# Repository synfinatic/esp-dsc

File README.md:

# ESP-DSC: Digital Setting Circles for ESP-12E/F

## About

Low cost alternative to my original Digital Setting Circles project the
[Teensy-DSC](https://github.com/synfinatic/teensy-dsc/).  This new design
uses the cheap ESP-12E/F WiFi enabled microcontroller which saves about 60% 
of the original price (~$40 vs ~$100).

I'm also planing to include the necessary .STL files so you can 3D print
the appropriate enclosure for the board.

More information about this project is available [on my website](https://synfin.net/sock_stream/tag/esp-dsc).

## v1.2 Status

 * Design PCB (complete!)
 * Port over the TeensyDSC code to the ESP-12 (complete!)
 * Verify that the ESP-12E is capable of handeling 2.5K PPR/10K count encoders (complete!)
 * Verify that the ESP-12E is capable of handeling 10K PPR/40K count encoders (failed!)
 * Create the necessary STL files to 3D print an enclosure for the board (complete!)
 * Major board change between v1.0 and v1.1- different pins used!

## v2.0 Status 
 * Redesign PCB for better performance  (TBD)
 * Update code based on new design (TBD)
 * Verify that the ESP-12E is capable of handeling 10k encoders (TBD)

## Performance

So a quick word about performance.  There are a number of people who claim that 
the ESP-12E has enough horsepower for two 2500PPR (10K after quadurature decoding) 
encoders.  One person told me they saw some errors, but they were small and 
likely caused by their mount.  This didn't seem very scientific to me, so I ran 
some tests.

My methodolgy is pretty simple.  I connected two ESP12E's to the same set of 
encoders.  Both ESP12E's used the same code and a custom modified version of 
[Paul Stoffgren's Encoder library](https://github.com/PaulStoffregen/Encoder) 
which has support for the ESP8266.  I also glued a toothpick to each encoder 
shaft to make it easier to rotate with my finger.  The test would be simple: If
both ESP12E's reported the same values, then I would say it was accurate.  But 
if the results were different, then it wasn't accurate.

I found that I could rotate a single 2,500PPR as fast as I possibly could 
without any error.  I could rotate a single 10,000PPR (40K after quadurature 
decoding) almost as fast without causing any error.

However, once I introduced a second encoder, I started seeing errors.  At about 
1 rotation/second, the 2500PPR encoders started to show some errors.  Two 
10,000PPR encoders had significant errors.  I also noticed that "flicking" the 
encoder causing it to quickly accellerate for a short duration (approx 1/4 
to 1/2 rotation) would cause significant errors even with the 2500PPR encoders.

This indicates that a person who does not very quickly move their scope 
should be able to use two 2500PPR encoders without introducing any 
errors.  If you're using a GoTo mount or a large scope you should be very 
safe.

I've done some testing on my AD12 (12" dobsonian) and 2500PPR/10,000 "count" 
encoders and found accuracy wasn't a problem at all.  The amount of error I saw
was approximagely +/-0.25deg meaning that if you have an EP with a 0.60deg 
effective FOV or more you should be able to use the ESP-DSC to point at an 
object and have it located inside your view through the scope.  Considering 
this is a mass produced dobsonian with a particile board mount, I consider 
this effectively within the error of the mount itself.

For comparison, my 30deg/82FOV Explore Scientific EP has an effective FOV of 
1.62deg in my scope which is more then twice the minimum.  

However I don't feel that it would be reliably accurate using 10,000PPR 
(40K count) encoders.  The result is I don't feel my initial PCB design is 
good enough with a single ESP12E.  I'm currently researching other solutions 
which could be implemented as cheaply and reliably as possible.

## Basic Features
I wanted to do my own digital setting circles (DSC) for my Apertura AD12.
The main goals were:

 * Support for at least 40K resolution via quadurature decoding (10k encoders)
 * Built in WiFi access point to allow wirelessly interfacing to an Apple iPad or Android tablet
 * Supporting at least [SkySafari Plus/Pro](http://www.skysafariastronomy.com/)
 * Powered via USB connection
 * Using industry standard RJ45 connection to encoders
 * Open source software & PCB design (GPLv3)
    * PCB Design done in [KiCad](http://www.kicad.org)
    * PCB's available from [OshPark](http://www.oshpark.com)
 * Inexpensive!  All the components should be available for < $40.

## Programming
You will need the Arduino 1.8.1+ IDE.   You will need to add support for the 
ESP8266 by [following the directions here](https://github.com/esp8266/Arduino).

Before you program your ESP-DSC you will need to:
 * Copy src/esp_dsc/config.h.sample to src/esp_dsc/config.h 
 * edit src/esp_dsc/config.h 

Under the tools menu, configure your board as follows:
 * Board: NodeMCU 1.0 (ESP-12E Module)
 * Flash Size: 4M (3M SPIFFS)
 * CPU Frequency: 80Mhz
 * Upload Speed: 115200 Baud

Do the following *exactly*:

 1. Disconnect the ESP-DSC from the encoders
 1. Connect a FTDI board to the FTDI header on the ESP-DSC and plug that into your computer
 1. Select the FTDI as your serial port in the Arduino IDE Tools menu
 1. Press and hold the Reset button
 1. Press and hold the Program button
 1. Release Reset button
 1. Release Program button
 1. Press the Upload button in the Arduino IDE Tools menu

## Supported Software

 * SkySafari Plus/Pro 
    - Select "Basic Encoder System"
    - Encoder Steps: Get Automatically
    - TCP Port 4030

## Similar Projects
There are a bunch of similar projects to ESP-DSC which you should be aware of:
 * [TeensyDSC](https://github.com/synfinatic/teensy-dsc/)
 * [Dave Ek's Setting Circles](http://eksfiles.net/digital-setting-circles/)
 * [mrosseel/arduino-dsc](https://github.com/mrosseel/arduino-dsc)
 * [mdw123/arduino-dsc](https://github.com/mdw123/arduino-dsc)
 * [Arduino Bluetooth DSC](http://orlygoingthirty.blogspot.com/2012/01/arduino-bluetooth-digital-setting.html)
 * [Mike Fulbright's Arduino DSC](http://msfastro.net/articles/arduinodsc/)
 * [Gigi's DSC w/ Magnetic Encoders](https://sites.google.com/site/gigimysite/home/astro/dsc-ekbox)

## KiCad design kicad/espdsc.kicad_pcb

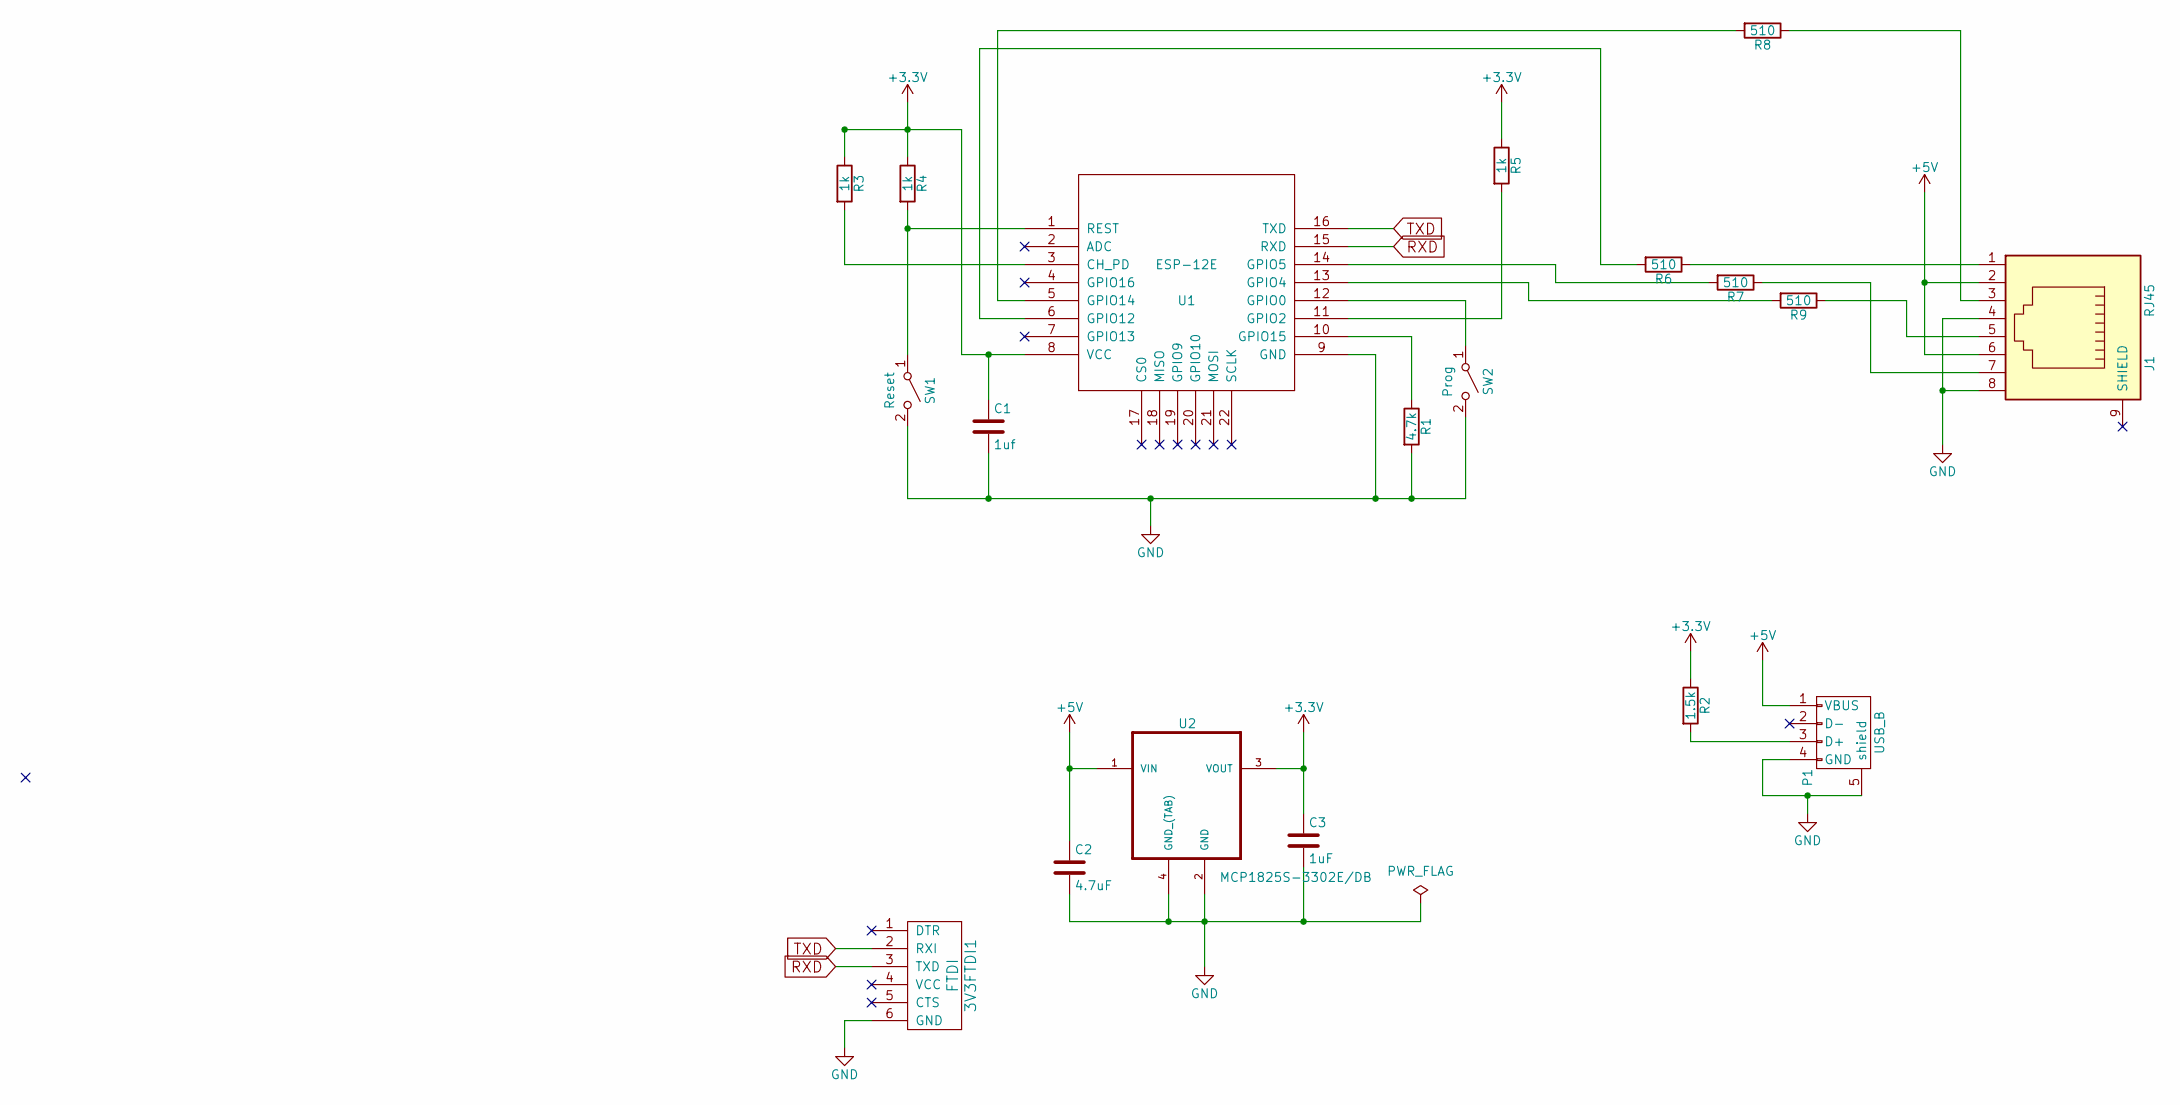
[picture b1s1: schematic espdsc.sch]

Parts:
3V3FTDI1: FTDI; FTDIHeader
C1: 1uf; C_0805_HandSoldering
C2: 4.7uF; C_0805_HandSoldering
C3: 1uF; C_0805_HandSoldering
J1: RJ45; RJ45_8
P1: USB_B
R1: 4.7k; R_0805_HandSoldering
R2: 1.5k; R_0805_HandSoldering
R3, R4, R5: 1k; R_0805_HandSoldering
R6, R7, R8, R9: 510; R_0805_HandSoldering
SW1: Reset; SPST-SMD-6x3.5
SW2: Prog; SPST-SMD-6x3.5
U1: ESP-12E; ESP-12E-SMD
U2: MCP1825S-3302E/DB; SOT-223

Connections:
+3V3: C1.1, C3.1, R2.1, R3.1, R4.1, R5.1, U1.8 (VCC), U2.3 (VOUT)
+5V: C2.1, J1.2, J1.6, P1.1 (VBUS), U2.1 (VIN)
GND: 3V3FTDI1.6 (GND), C1.2, C2.2, C3.2, J1.4, J1.8, P1.4 (GND), P1.5 (shield), R1.2, SW1.2 (B), SW2.2 (B), U1.9 (GND), U2.2 (GND), U2.4 (GND_(TAB))
unnamed: J1.1, R6.1
unnamed: J1.3, R8.1
unnamed: J1.5, R9.1
unnamed: J1.7, R7.1
unnamed: P1.3 (D+), R2.2
unnamed: R1.1, U1.10 (GPIO15)
unnamed: R3.2, U1.3 (CH_PD)
unnamed: R4.2, SW1.1 (A), U1.1 (REST)
unnamed: R5.2, U1.11 (GPIO2)
unnamed: R6.2, U1.6 (GPIO12)
unnamed: R7.2, U1.14 (GPIO5)
unnamed: R8.2, U1.5 (GPIO14)
unnamed: R9.2, U1.13 (GPIO4)
unnamed: SW2.1 (A), U1.12 (GPIO0)
RXD: 3V3FTDI1.3 (TXD), U1.15 (RXD)
TXD: 3V3FTDI1.2 (RXI), U1.16 (TXD)

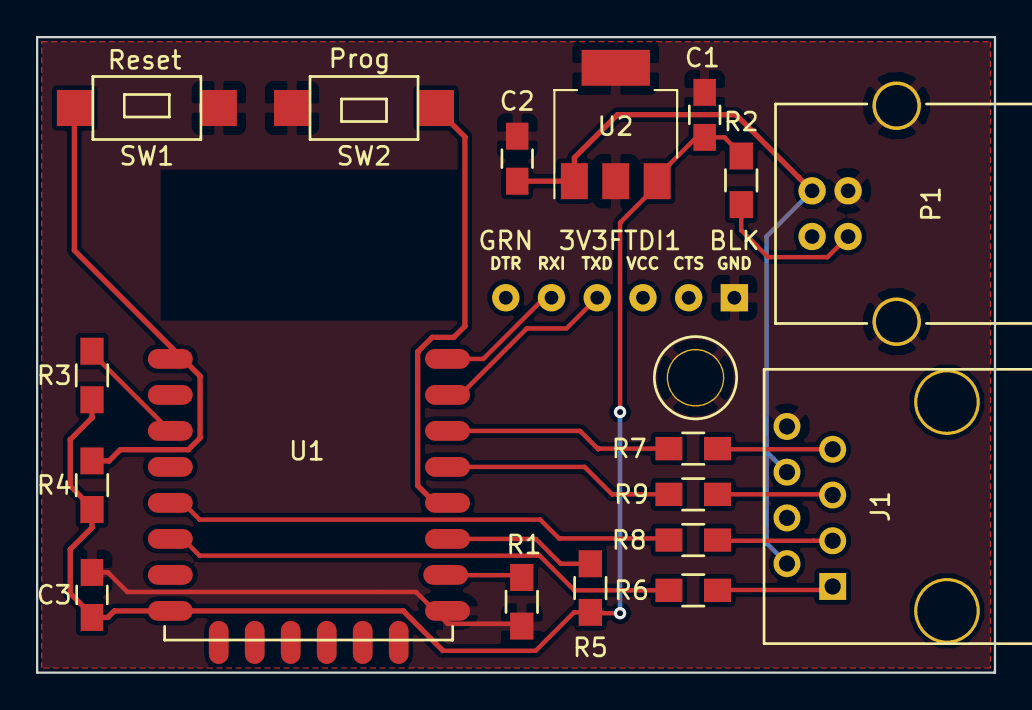
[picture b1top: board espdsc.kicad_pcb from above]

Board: 2 copper layers, 53.2 x 35.3 mm, 19 parts (0 on the bottom side), 19 nets.

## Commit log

2017-02-27 v1.0 design
    Completely untested.
2017-03-17 update design for v1.0 release
2017-03-17 Add license file
2017-03-18 First pass at encoder decoding
    POC for using interrupts and global volatile variables. Code seems
    to at first glance work and seems to be able to accurately track
    two 2.5 (native)/10K (quadrature) encoders
2017-03-19 Working, basic bench tested code
    - Doesn't support setting the encoder resolution (yet)
    - Seems to handle both interrupts and the WiFi just fine
    - Supports both SoftAP and Client mode!
2017-03-19 Major code improvements & docs
    - Improve docs for users
    - Add more commands (get version, get/set resolution of encoders)
    - Move local config to config.h
2017-03-19 Small tweaks to code. Document future plans
2017-03-19 Fix encoder pins & optimize interrupts
    - The RA/Dec pins were swapped
    - Try to optimize handing of interrupts. Testing with 2.5k CPR encoders
    shows that I wasn't fully sucessful yet.
2017-03-20 more optimizations (which don't work)
    Saving this mostly for posterity as even after removing (most of) the
    digitalRead() calls, we can't keep up with 2 encoders. Going to need
    to investigate alternatives documented in TODO.md
2017-03-24 Make code easier to debug
2017-03-26 Add support for Encoder library and better debugging
2017-04-04 update readme with performance test results
2017-05-03 Basic working code
    Remove all the crap that we don't need anymore since we're done testing
    different methods of trying to keep up with the newer high resolution
    encoders (above 2500PPR/10K "count"). This just uses the Encoder
    library which is stable and works well.
    Code has been tested using my telescope and seems to work great with
    SkySafari!
2017-05-03 update readme with results of my testing
2017-05-05 Add STL and Fusion360 case files for v1.0 case
2017-05-05 clarify testing results
2017-07-04 fixes for neg encoder resolution
    merged from TeensyDSC
2017-12-03 v1.1 board & code
    - Move GPIO2/15 to GPIO14/12 to avoid boot conflict
    - Remove level shifter and replace with 4x 150Ohm resistors
    - Tweak RJ45 footprint for better fit
    - Add pullup for D+ on USB
    - Remove 3.3V FTDI jumper
    - Move Reset button label
2017-12-03 v1.2
    - Switch ESP12E to pure SMD footprint
2018-02-11 add another related project
2021-11-10 Update README.md
    https://forum.kicad.info/t/warning-avoid-all-links-to-kicad-pcb-org-use-kicad-org/31521
